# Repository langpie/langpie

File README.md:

# langpie 项目

# 树莓派分布式自动驾驶小车项目-浪派项目
## Respberry Pi LangPie Open Source Project

## 项目目标
* V1.0 阶段: 让树莓派小车能够跑起来(浪)
* V2.0 阶段: 让树莓派能够狠狠的浪(例如加入机器视觉)
* V3.0 阶段: 让树莓派能够狂浪(能够浪到指定地点)
* V4.0 阶段: 让每个人的树莓派能够一起浪(浪派对)
* V5.0 阶段: 让树莓派能够用神经网络自己判断自己该去哪里浪(放浪形骸)
* V6.0 阶段: 树莓派贾维斯浪催的小犊子(没谱)

## 目前状态
### V1.0 版本
- [ ] 电路图绘制
- [ ] 机械图绘制
- [ ] 电路图 Layout
- [ ] 电路板打板
- [ ] 购买元器件
- [ ] 设备焊接
- [ ] 小车组装
- [ ] 树莓派系统安装
- [ ] wiringPi 安装调试
- [ ] 测试电源
- [ ] 测试充电
- [ ] 测试马达
- [ ] 测试树莓派驱动
- [ ] 测试 OLED 屏幕
- [ ] 测试LED 灯
 
## 项目组成员 including Email：

* 圈圈  bg3mdo#langpie.ga
* 漂移菌  yoyojack#langpie.ga
* DoubleDog  doubledog#langpie.ga
* hahaha  hahaha#langpie.ga
* 刘津屹  liujinyi#langpie.ga
* 中华绘图铅笔  pencil#langpie.ga
* 飞鸿  bg3nit#langpie.ga
* 洋洋大叔  bi3qdn#langpie.ga
* 祁建鑫  qjx#langpie.ga
* wjcwqc  wjcwqc#langpie.ga
* 小白 dmuxiaobai#langpie.ga
* lqh  lqh#langpie.ga
* kwanghue kwanghue#langpie.ga
* 张翼 zy#langpie.ga
* iChizer0 

##  项目站点 Project website: 

www.langpie.ga

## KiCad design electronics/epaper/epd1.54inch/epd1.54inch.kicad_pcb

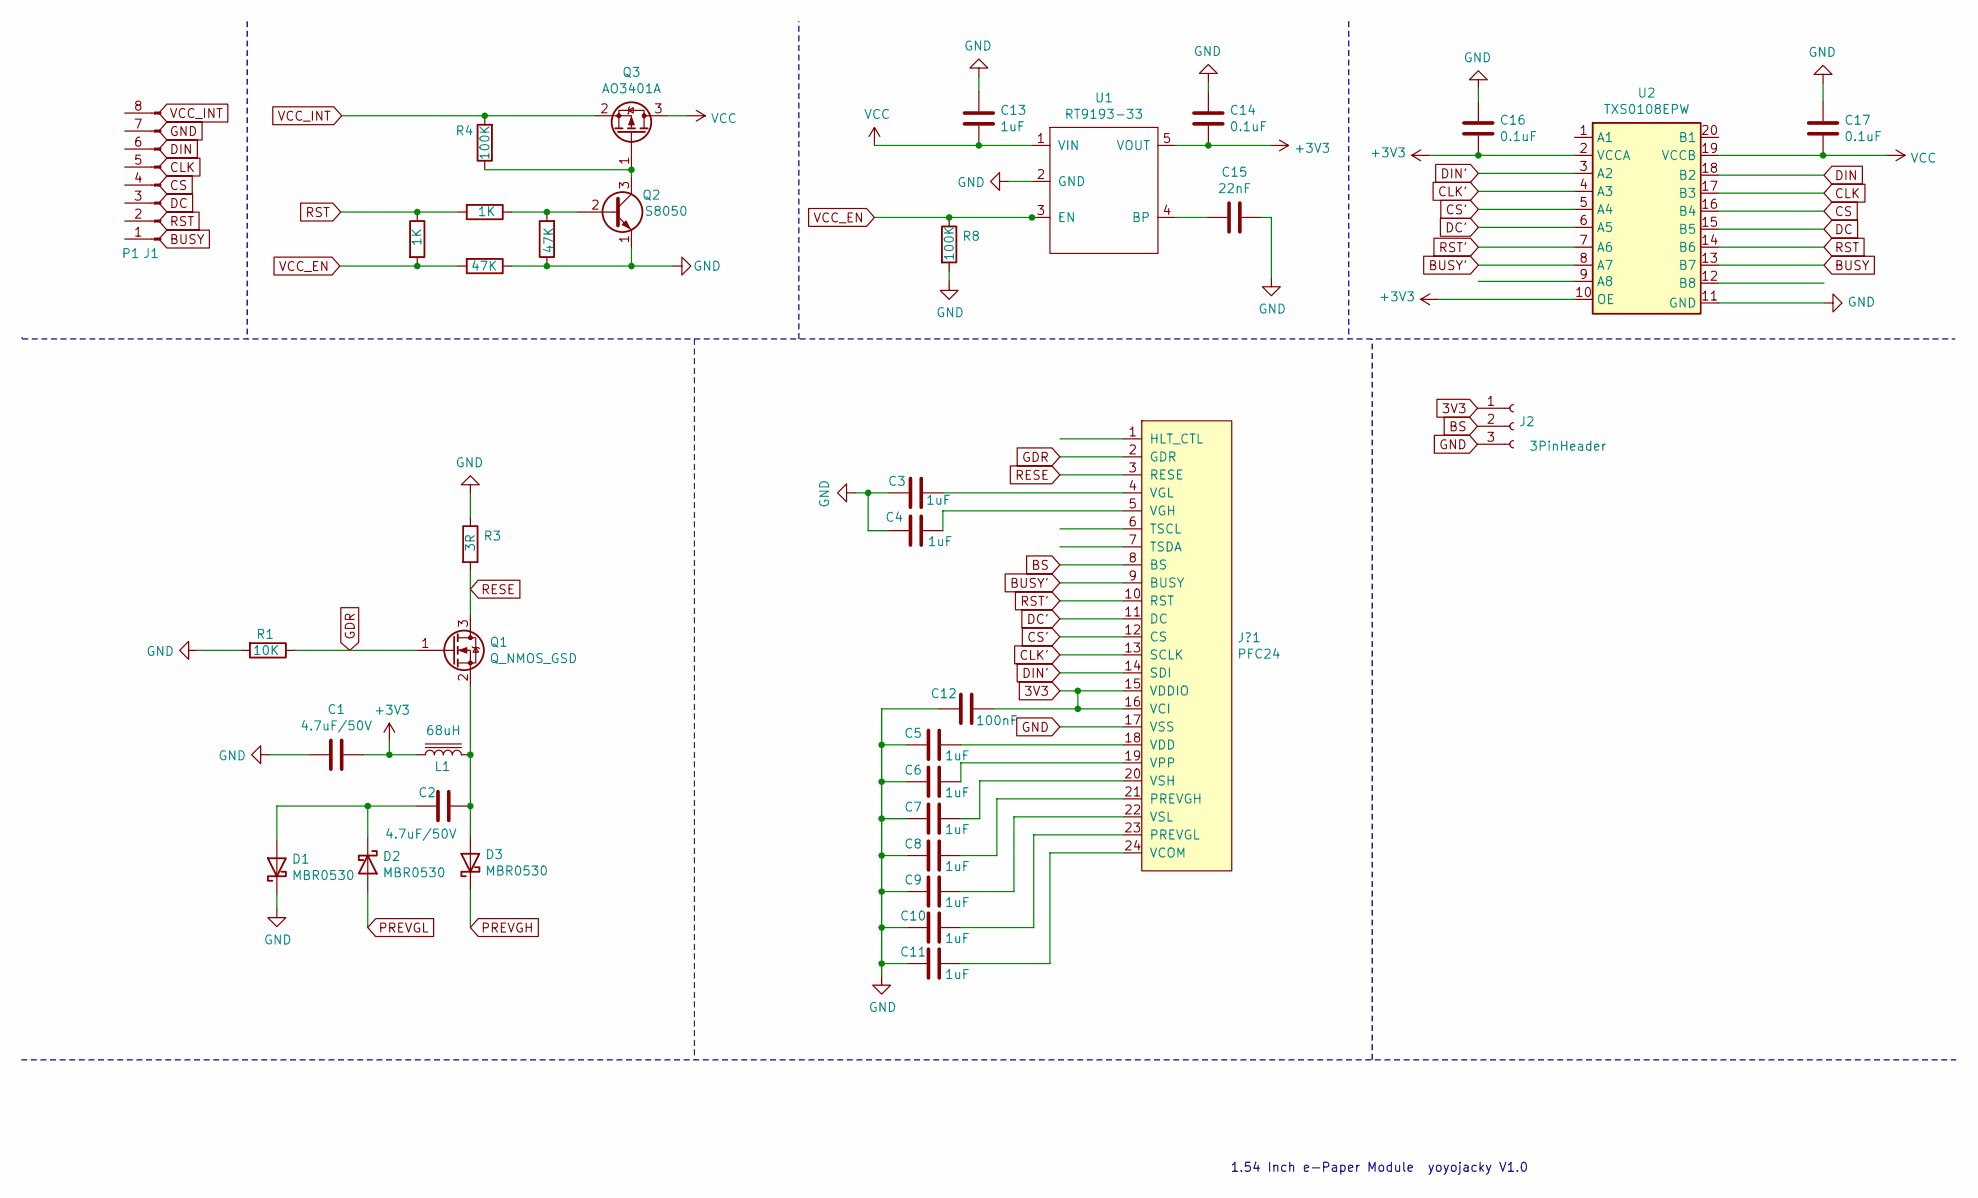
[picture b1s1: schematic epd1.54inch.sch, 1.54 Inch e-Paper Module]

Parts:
C1, C2: 4.7uF/50V; C_0603_1608Metric_Pad1.05x0.95mm_HandSolder
C3, C4, C5, C6, C7, C8, C9, C10, C11, C13: 1uF; C_0603_1608Metric_Pad1.05x0.95mm_HandSolder
C12: 100nF; C_0603_1608Metric_Pad1.05x0.95mm_HandSolder
C14, C16, C17: 0.1uF; C_0603_1608Metric_Pad1.05x0.95mm_HandSolder
C15: 22nF; C_0603_1608Metric_Pad1.05x0.95mm_HandSolder
D1, D2, D3: MBR0530; D_SOD-123
J1: P1; PinHeader_1x08_P2.54mm_Vertical
J2: 3PinHeader; PinHeader_1x03_P2.54mm_Vertical
J?1: PFC24; Hirose_FH12-24S-0.5SH_1x24-1MP_P0.50mm_Horizontal
L1: 68uH; L_10.4x10.4_H4.8
Q1: Q_NMOS_GSD; SOT-323_SC-70_Handsoldering
Q2: S8050; TO-92_Inline
Q3: AO3401A; SOT-23
R1: 10K; R_0603_1608Metric_Pad1.05x0.95mm_HandSolder
R2, R5: 1K; R_0603_1608Metric_Pad1.05x0.95mm_HandSolder
R3: 3R; R_0603_1608Metric_Pad1.05x0.95mm_HandSolder
R4, R8: 100K; R_0603_1608Metric_Pad1.05x0.95mm_HandSolder
R6, R7: 47K; R_0603_1608Metric_Pad1.05x0.95mm_HandSolder
U1: RT9193-33; SOT-23-5
U2: TXS0108EPW; TSSOP-20_4.4x6.5mm_P0.65mm

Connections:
3V3: C12.1, J2.1, J?1.15 (VDDIO), J?1.16 (VCI)
+3V3: C1.1, C14.2, C16.2, L1.1, U1.5 (VOUT), U2.2 (VCCA), U2.10 (OE)
BS: J2.2, J?1.8 (BS)
BUSY: U2.13 (B7)
BUSY': J?1.9 (BUSY), U2.8 (A7)
CLK: U2.17 (B3)
CLK': J?1.13 (SCLK), U2.4 (A3)
CS: U2.16 (B4)
CS': J?1.12 (CS), U2.5 (A4)
DC: U2.15 (B5)
DC': J?1.11 (DC), U2.6 (A5)
DIN: U2.18 (B2)
DIN': J?1.14 (SDI), U2.3 (A2)
GDR: J?1.2 (GDR), Q1.1 (G), R1.1
GND: C1.2, C3.2, C4.2, C5.2, C6.2, C7.2, C8.2, C9.2, C10.2, C11.2, C12.2, C13.2, C14.1, C15.1, C16.1, C17.1, D1.1 (K), J2.3, J?1.17 (VSS), Q2.1 (E), R1.2, R3.1, R6.1, R7.1, R8.2, U1.2 (GND), U2.11 (GND)
unnamed: C2.1, D1.2 (A), D2.1 (K)
unnamed: C2.2, D3.2 (A), L1.2, Q1.2 (S)
unnamed: C3.1, J?1.4 (VGL)
unnamed: C4.1, J?1.5 (VGH)
unnamed: C5.1, J?1.18 (VDD)
unnamed: C6.1, J?1.19 (VPP)
unnamed: C7.1, J?1.20 (VSH)
unnamed: C8.1, J?1.21 (PREVGH)
unnamed: C9.1, J?1.22 (VSL)
unnamed: C10.1, J?1.23 (PREVGL)
unnamed: C11.1, J?1.24 (VCOM)
unnamed: C15.2, U1.4 (BP)
unnamed: Q2.2 (B), R5.1, R7.2
unnamed: Q2.3 (C), Q3.1 (G), R4.1
PREVGH: D3.1 (K)
PREVGL: D2.2 (A)
RESE: J?1.3 (RESE), Q1.3 (D), R3.2
RST: R2.1, R5.2, U2.14 (B6)
RST': J?1.10 (RST), U2.7 (A6)
VCC: C13.1, C17.2, Q3.3 (D), U1.1 (VIN), U2.19 (VCCB)
VCC_EN: R2.2, R6.2, R8.1, U1.3 (EN)
VCC_INT: Q3.2 (S), R4.2

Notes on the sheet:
1.54 Inch e-Paper Module yoyojacky V1.0

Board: 2 copper layers, 37 parts (0 on the bottom side), 30 nets, no tracks yet.

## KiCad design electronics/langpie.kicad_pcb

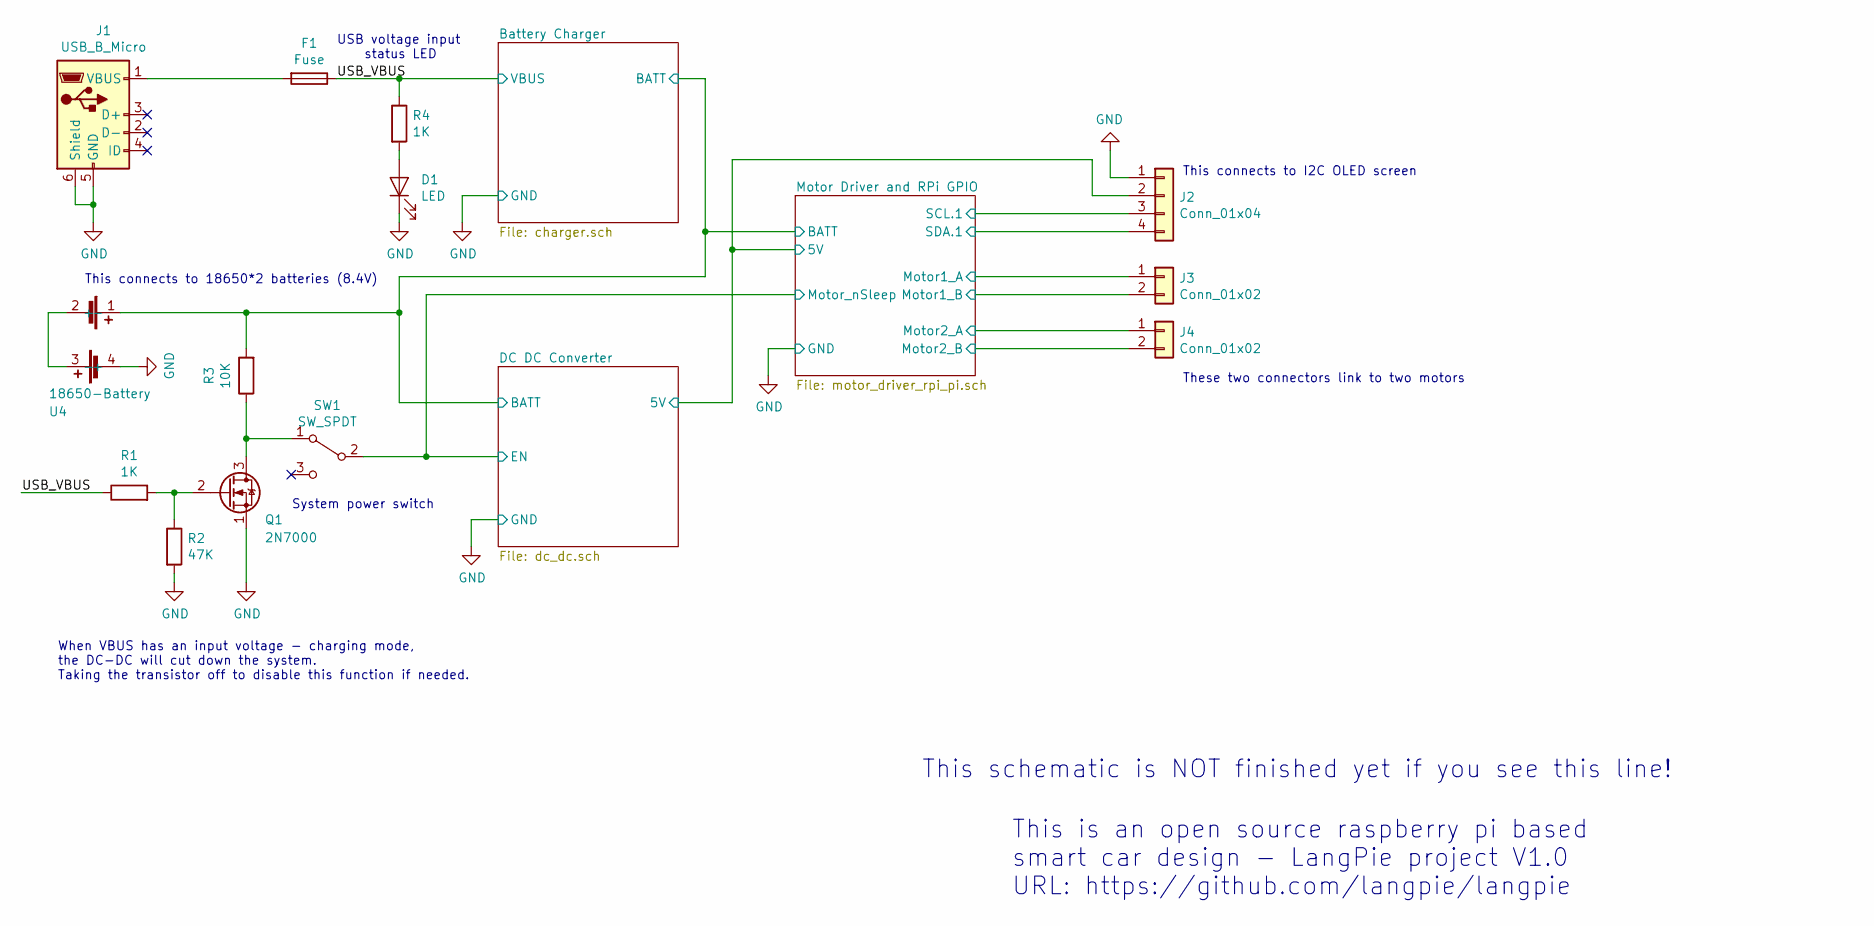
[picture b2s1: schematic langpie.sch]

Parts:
D1: LED; LED_0805_2012Metric
F1: Fuse; Fuse_1206_3216Metric
J1: USB_B_Micro; USB_Micro-B_GCT_USB3076-30-A
J2: Conn_01x04; PinHeader_1x04_P2.54mm_Vertical
J3, J4: Conn_01x02; SolderWirePad_1x02_P5.08mm_Drill1.5mm
Q1: 2N7000; SOT-23
R1, R4: 1K; R_0805_2012Metric
R2: 47K; R_0805_2012Metric
R3: 10K; R_0805_2012Metric
SW1: SW_SPDT; SW_CuK_OS102011MA1QN1_SPDT_Angled
U4: 18650-Battery; li-battery-case

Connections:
/Battery Charger/BATT: R3.2, U4.1 (+); also elsewhere on the board
/DC DC Converter/5V: J2.2; also elsewhere on the board
/DC DC Converter/EN: SW1.2 (B); also elsewhere on the board
/Motor Driver and RPi GPIO/Motor1_A: J3.1; also elsewhere on the board
/Motor Driver and RPi GPIO/Motor1_B: J3.2; also elsewhere on the board
/Motor Driver and RPi GPIO/Motor2_A: J4.1; also elsewhere on the board
/Motor Driver and RPi GPIO/Motor2_B: J4.2; also elsewhere on the board
/Motor Driver and RPi GPIO/SCL.1: J2.3; also elsewhere on the board
/Motor Driver and RPi GPIO/SDA.1: J2.4; also elsewhere on the board
/USB_VBUS: F1.1, R1.1, R4.1; also elsewhere on the board
GND: D1.1 (K), J1.5 (GND), J1.6 (Shield), J2.1, Q1.1 (S), R2.2, U4.4 (-); also elsewhere on the board
unnamed: D1.2 (A), R4.2
unnamed: F1.2, J1.1 (VBUS)
unnamed: Q1.2 (G), R1.2, R2.1
unnamed: Q1.3 (D), R3.1, SW1.1 (A)
unnamed: U4.2 (-), U4.3 (+)

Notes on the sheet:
When VBUS has an input voltage - charging mode, the DC-DC will cut down the system. Taking the transistor off to disable this function if needed.
USB voltage input status LED
This connects to I2C OLED screen
This connects to 18650*2 batteries (8.4V)
These two connectors link to two motors
System power switch
This is an open source raspberry pi based smart car design - LangPie project V1.0 URL: https://github.com/langpie/langpie
This schematic is NOT finished yet if you see this line!

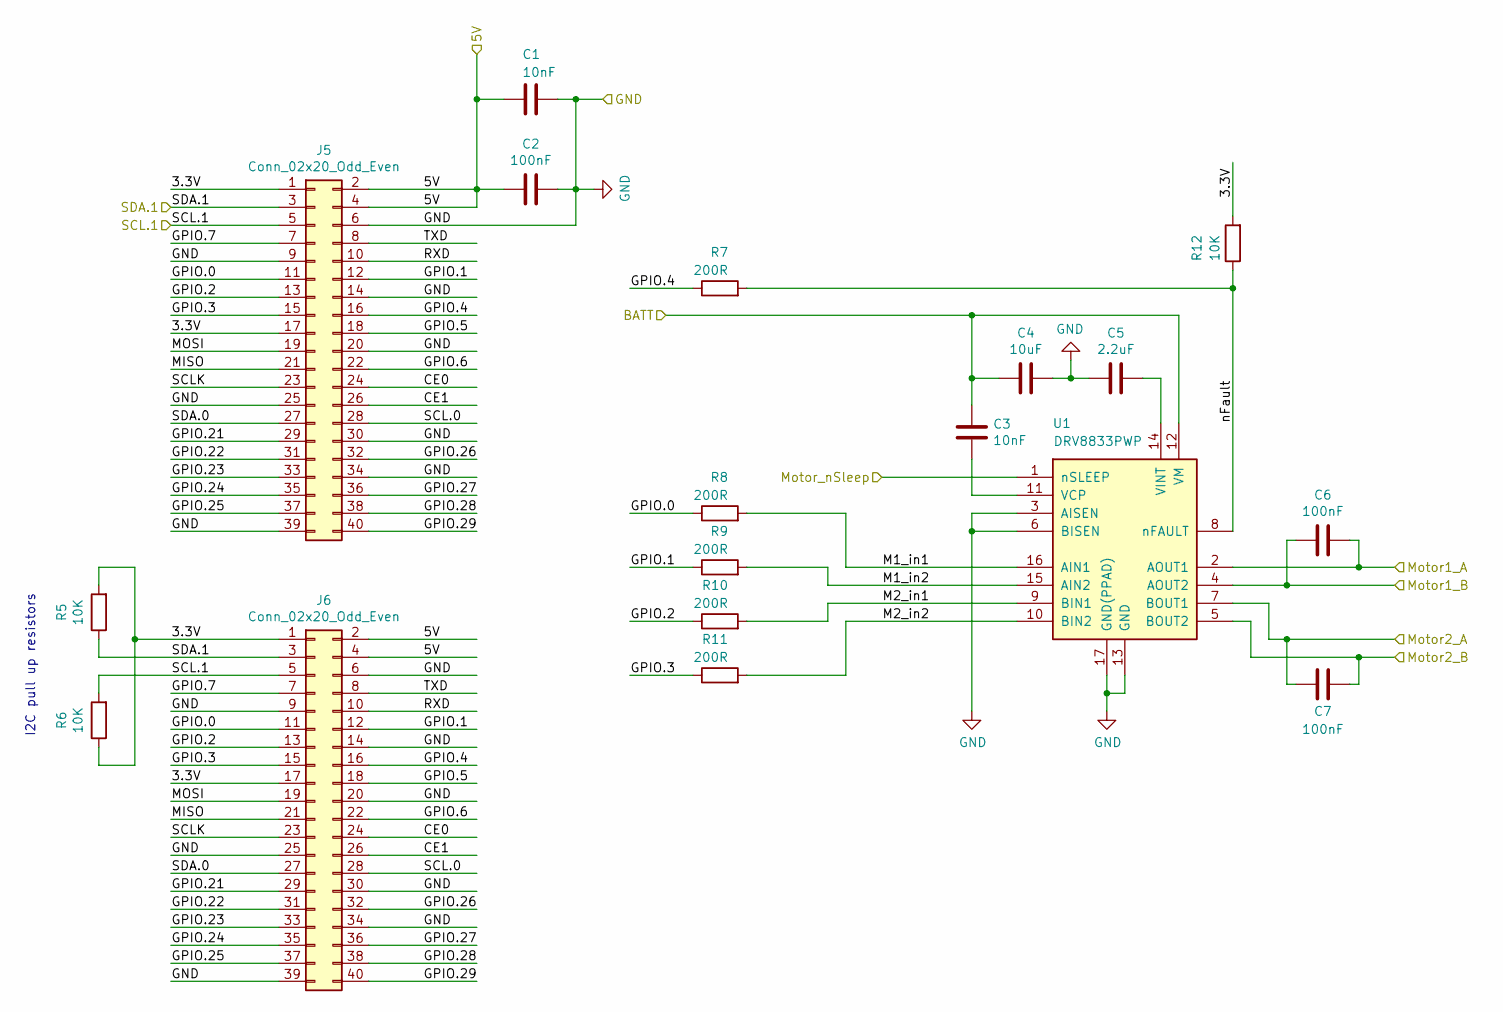
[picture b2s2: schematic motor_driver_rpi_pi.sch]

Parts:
C1, C3: 10nF
C2, C6, C7: 100nF
C4: 10uF
C5: 2.2uF
J5, J6: Conn_02x20_Odd_Even
R5, R6, R12: 10K; R_0805_2012Metric
R7, R8, R9, R10, R11: 200R; R_0805_2012Metric
U1: DRV8833PWP; HTSSOP-16-1EP_4.4x5mm_P0.65mm_EP3.4x5mm_Mask2.46x2.31mm_The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

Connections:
/Battery Charger/BATT: C3.1, C4.2, U1.12 (VM); also elsewhere on the board
/DC DC Converter/5V: C1.2, C2.2, J5.2, J5.4, J6.2, J6.4; also elsewhere on the board
/DC DC Converter/EN: U1.1 (nSLEEP); also elsewhere on the board
/Motor Driver and RPi GPIO/3.3V: J5.1, J5.17, J6.1, J6.17, R5.2, R6.1, R12.2
/Motor Driver and RPi GPIO/CE0: J5.24, J6.24
/Motor Driver and RPi GPIO/CE1: J5.26, J6.26
/Motor Driver and RPi GPIO/GPIO.0: J5.11, J6.11, R8.1
/Motor Driver and RPi GPIO/GPIO.1: J5.12, J6.12, R9.1
/Motor Driver and RPi GPIO/GPIO.2: J5.13, J6.13, R10.1
/Motor Driver and RPi GPIO/GPIO.3: J5.15, J6.15, R11.1
/Motor Driver and RPi GPIO/GPIO.4: J5.16, J6.16, R7.1
/Motor Driver and RPi GPIO/GPIO.5: J5.18, J6.18
/Motor Driver and RPi GPIO/GPIO.6: J5.22, J6.22
/Motor Driver and RPi GPIO/GPIO.7: J5.7, J6.7
/Motor Driver and RPi GPIO/GPIO.21: J5.29, J6.29
/Motor Driver and RPi GPIO/GPIO.22: J5.31, J6.31
/Motor Driver and RPi GPIO/GPIO.23: J5.33, J6.33
/Motor Driver and RPi GPIO/GPIO.24: J5.35, J6.35
/Motor Driver and RPi GPIO/GPIO.25: J5.37, J6.37
/Motor Driver and RPi GPIO/GPIO.26: J5.32, J6.32
/Motor Driver and RPi GPIO/GPIO.27: J5.36, J6.36
/Motor Driver and RPi GPIO/GPIO.28: J5.38, J6.38
/Motor Driver and RPi GPIO/GPIO.29: J5.40, J6.40
/Motor Driver and RPi GPIO/M1_in1: R8.2, U1.16 (AIN1)
/Motor Driver and RPi GPIO/M1_in2: R9.2, U1.15 (AIN2)
/Motor Driver and RPi GPIO/M2_in1: R10.2, U1.9 (BIN1)
/Motor Driver and RPi GPIO/M2_in2: R11.2, U1.10 (BIN2)
/Motor Driver and RPi GPIO/MISO: J5.21, J6.21
/Motor Driver and RPi GPIO/MOSI: J5.19, J6.19
/Motor Driver and RPi GPIO/Motor1_A: C6.1, U1.2 (AOUT1); also elsewhere on the board
/Motor Driver and RPi GPIO/Motor1_B: C6.2, U1.4 (AOUT2); also elsewhere on the board
/Motor Driver and RPi GPIO/Motor2_A: C7.2, U1.7 (BOUT1); also elsewhere on the board
/Motor Driver and RPi GPIO/Motor2_B: C7.1, U1.5 (BOUT2); also elsewhere on the board
/Motor Driver and RPi GPIO/RXD: J5.10, J6.10
/Motor Driver and RPi GPIO/SCL.0: J5.28, J6.28
/Motor Driver and RPi GPIO/SCL.1: J5.5, J6.5, R6.2; also elsewhere on the board
/Motor Driver and RPi GPIO/SCLK: J5.23, J6.23
/Motor Driver and RPi GPIO/SDA.0: J5.27, J6.27
/Motor Driver and RPi GPIO/SDA.1: J5.3, J6.3, R5.1; also elsewhere on the board
/Motor Driver and RPi GPIO/TXD: J5.8, J6.8
/Motor Driver and RPi GPIO/nFault: R7.2, R12.1, U1.8 (nFAULT)
GND: C1.1, C2.1, C4.1, C5.2, J5.6, J5.9, J5.14, J5.20, J5.25, J5.30, J5.34, J5.39, J6.6, J6.9, J6.14, J6.20, J6.25, J6.30, J6.34, J6.39, U1.3 (AISEN), U1.6 (BISEN), U1.13 (GND), U1.17 (GND(PPAD)); also elsewhere on the board
unnamed: C3.2, U1.11 (VCP)
unnamed: C5.1, U1.14 (VINT)

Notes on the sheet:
I2C pull up resistors

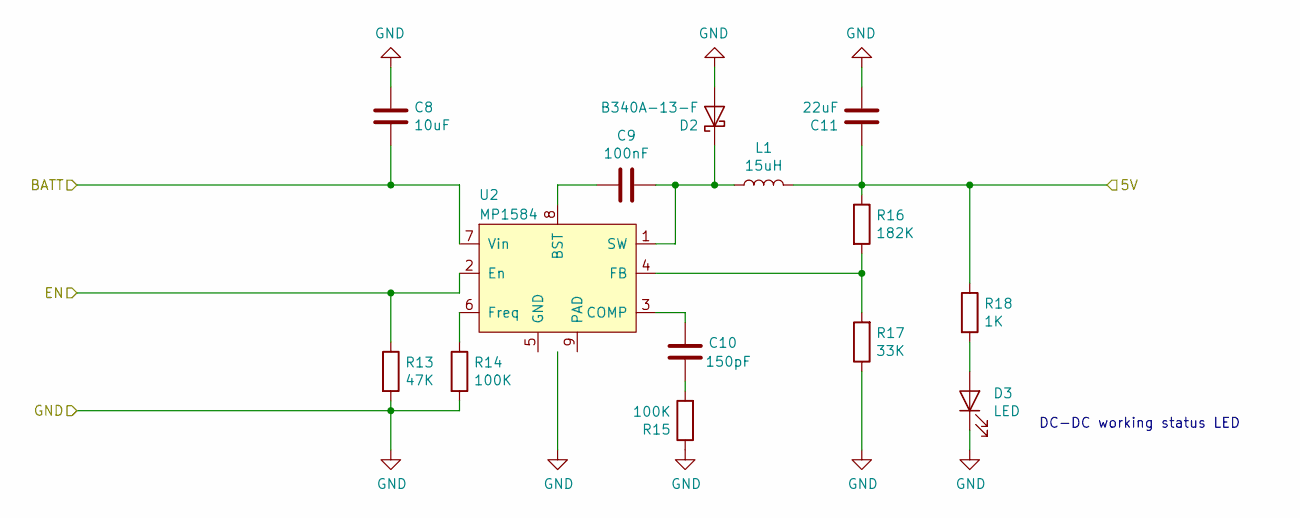
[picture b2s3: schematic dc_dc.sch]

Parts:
C8: 10uF; C_1206_3216Metric
C9: 100nF; C_0805_2012Metric
C10: 150pF; C_0805_2012Metric
C11: 22uF; C_1206_3216Metric
D2: B340A-13-F; D_SMA
D3: LED; LED_0805_2012Metric
L1: 15uH; L_12x12mm_H6mm
R13: 47K; R_0805_2012Metric
R14, R15: 100K; R_0805_2012Metric
R16: 182K; R_0805_2012Metric
R17: 33K; R_0805_2012Metric
R18: 1K; R_0805_2012Metric
U2: MP1584; SOIC-8-1EP_3.9x4.9mm_P1.27mm_EP2.29x3mm_ThermalVias

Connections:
/Battery Charger/BATT: C8.2, U2.7 (Vin); also elsewhere on the board
/DC DC Converter/5V: C11.1, L1.2, R16.1, R18.1; also elsewhere on the board
/DC DC Converter/EN: R13.1, U2.2 (En); also elsewhere on the board
GND: C8.1, C11.2, D2.2 (A), D3.1 (K), R13.2, R14.2, R15.1, R17.1, U2.5 (GND), U2.9 (PAD); also elsewhere on the board
unnamed: C9.1, D2.1 (K), L1.1, U2.1 (SW)
unnamed: C9.2, U2.8 (BST)
unnamed: C10.1, U2.3 (COMP)
unnamed: C10.2, R15.2
unnamed: D3.2 (A), R18.2
unnamed: R14.1, U2.6 (Freq)
unnamed: R16.2, R17.2, U2.4 (FB)

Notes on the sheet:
DC-DC working status LED

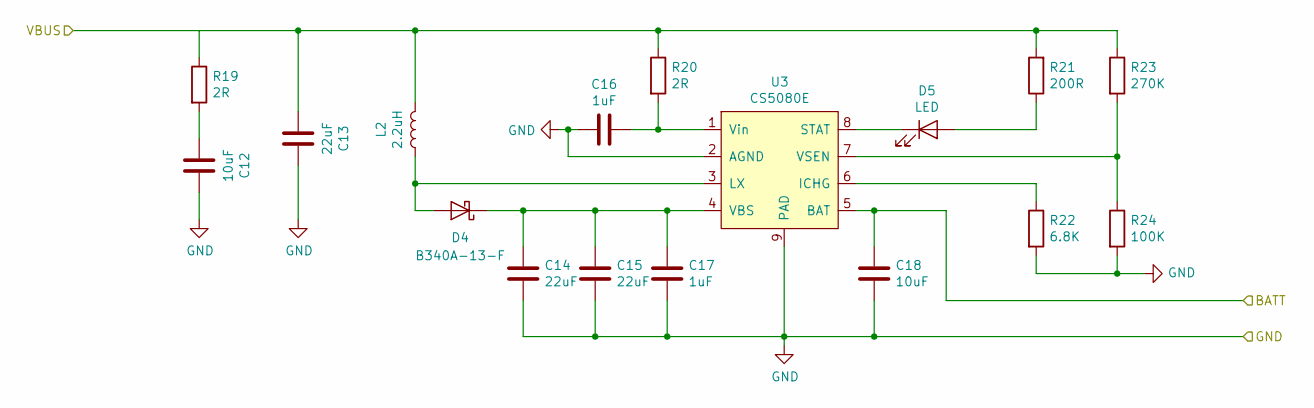
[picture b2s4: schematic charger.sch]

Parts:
C12, C18: 10uF; C_1206_3216Metric
C13, C14, C15: 22uF; C_1206_3216Metric
C16, C17: 1uF; C_0805_2012Metric
D4: B340A-13-F; D_SMA
D5: LED; LED_0805_2012Metric
L2: 2.2uH; L_12x12mm_H6mm
R19, R20: 2R; R_0805_2012Metric
R21: 200R; R_0805_2012Metric
R22: 6.8K; R_0805_2012Metric
R23: 270K; R_0805_2012Metric
R24: 100K; R_0805_2012Metric
U3: CS5080E; SOIC-8-1EP_3.9x4.9mm_P1.27mm_EP2.29x3mm_ThermalVias

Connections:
/Battery Charger/BATT: C18.1, U3.5 (BAT); also elsewhere on the board
/USB_VBUS: C13.2, L2.2, R19.1, R20.1, R21.2, R23.1; also elsewhere on the board
GND: C12.1, C13.1, C14.1, C15.1, C16.2, C17.1, C18.2, R22.2, R24.2, U3.2 (AGND), U3.9 (PAD); also elsewhere on the board
unnamed: C12.2, R19.2
unnamed: C14.2, C15.2, C17.2, D4.1 (K), U3.4 (VBS)
unnamed: C16.1, R20.2, U3.1 (Vin)
unnamed: D4.2 (A), L2.1, U3.3 (LX)
unnamed: D5.1 (K), U3.8 (STAT)
unnamed: D5.2 (A), R21.1
unnamed: R22.1, U3.6 (ICHG)
unnamed: R23.2, R24.1, U3.7 (VSEN)

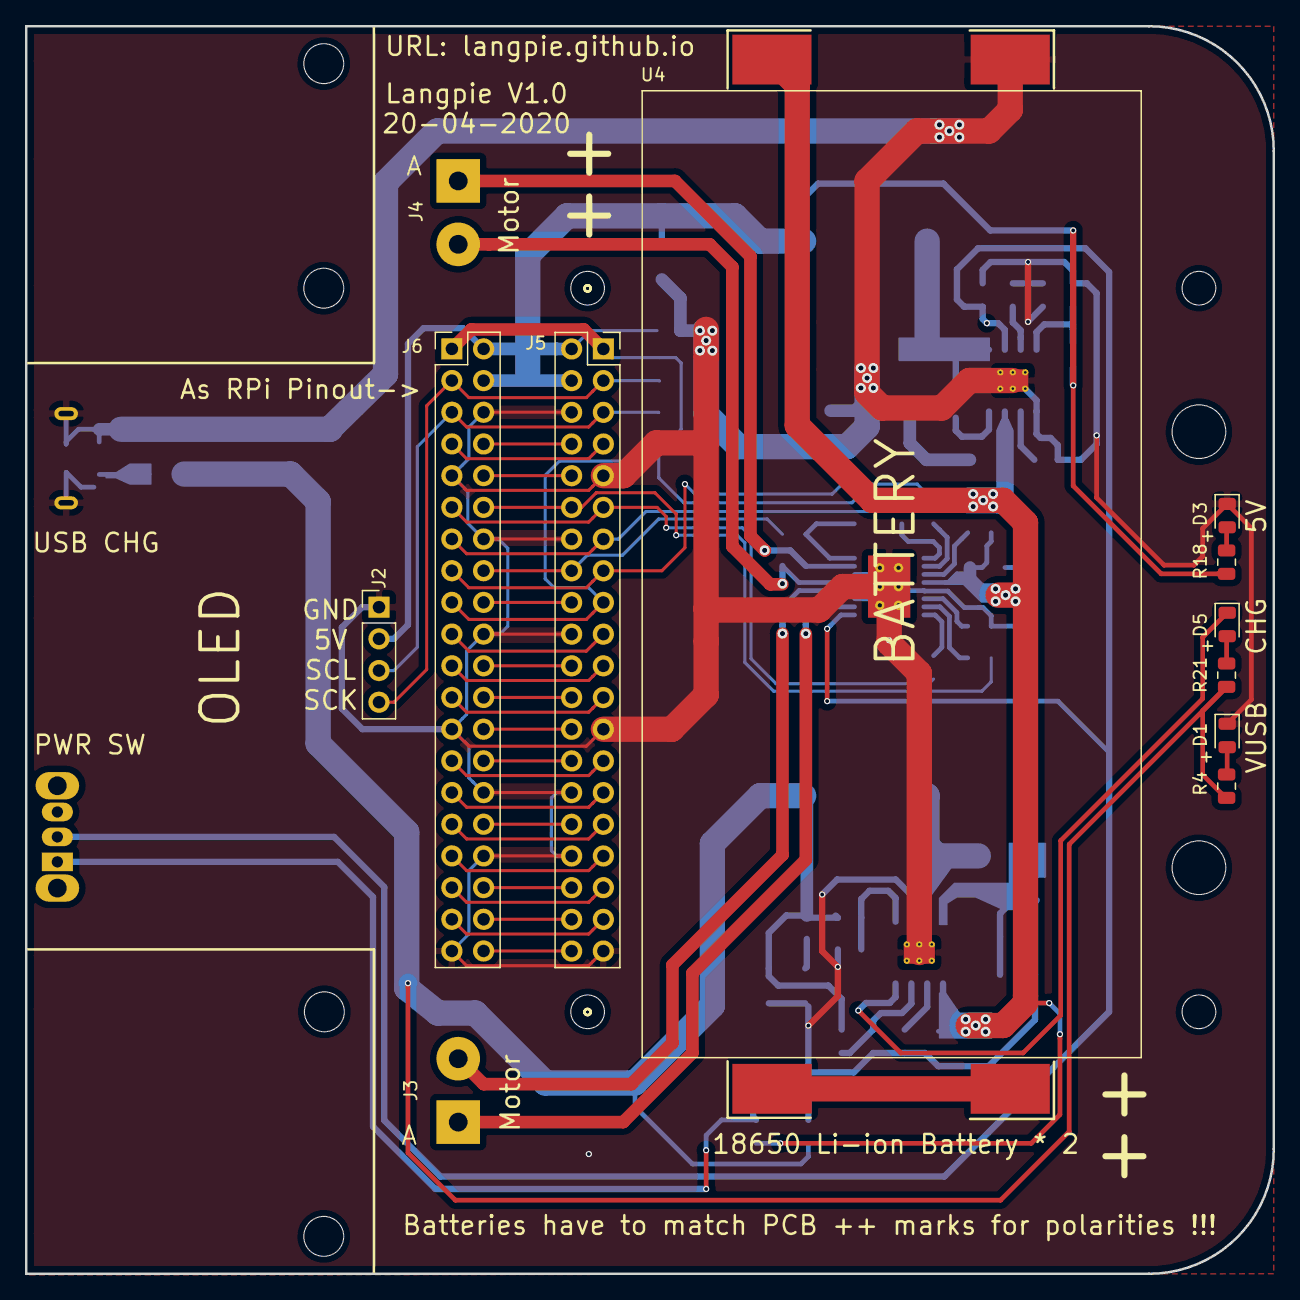
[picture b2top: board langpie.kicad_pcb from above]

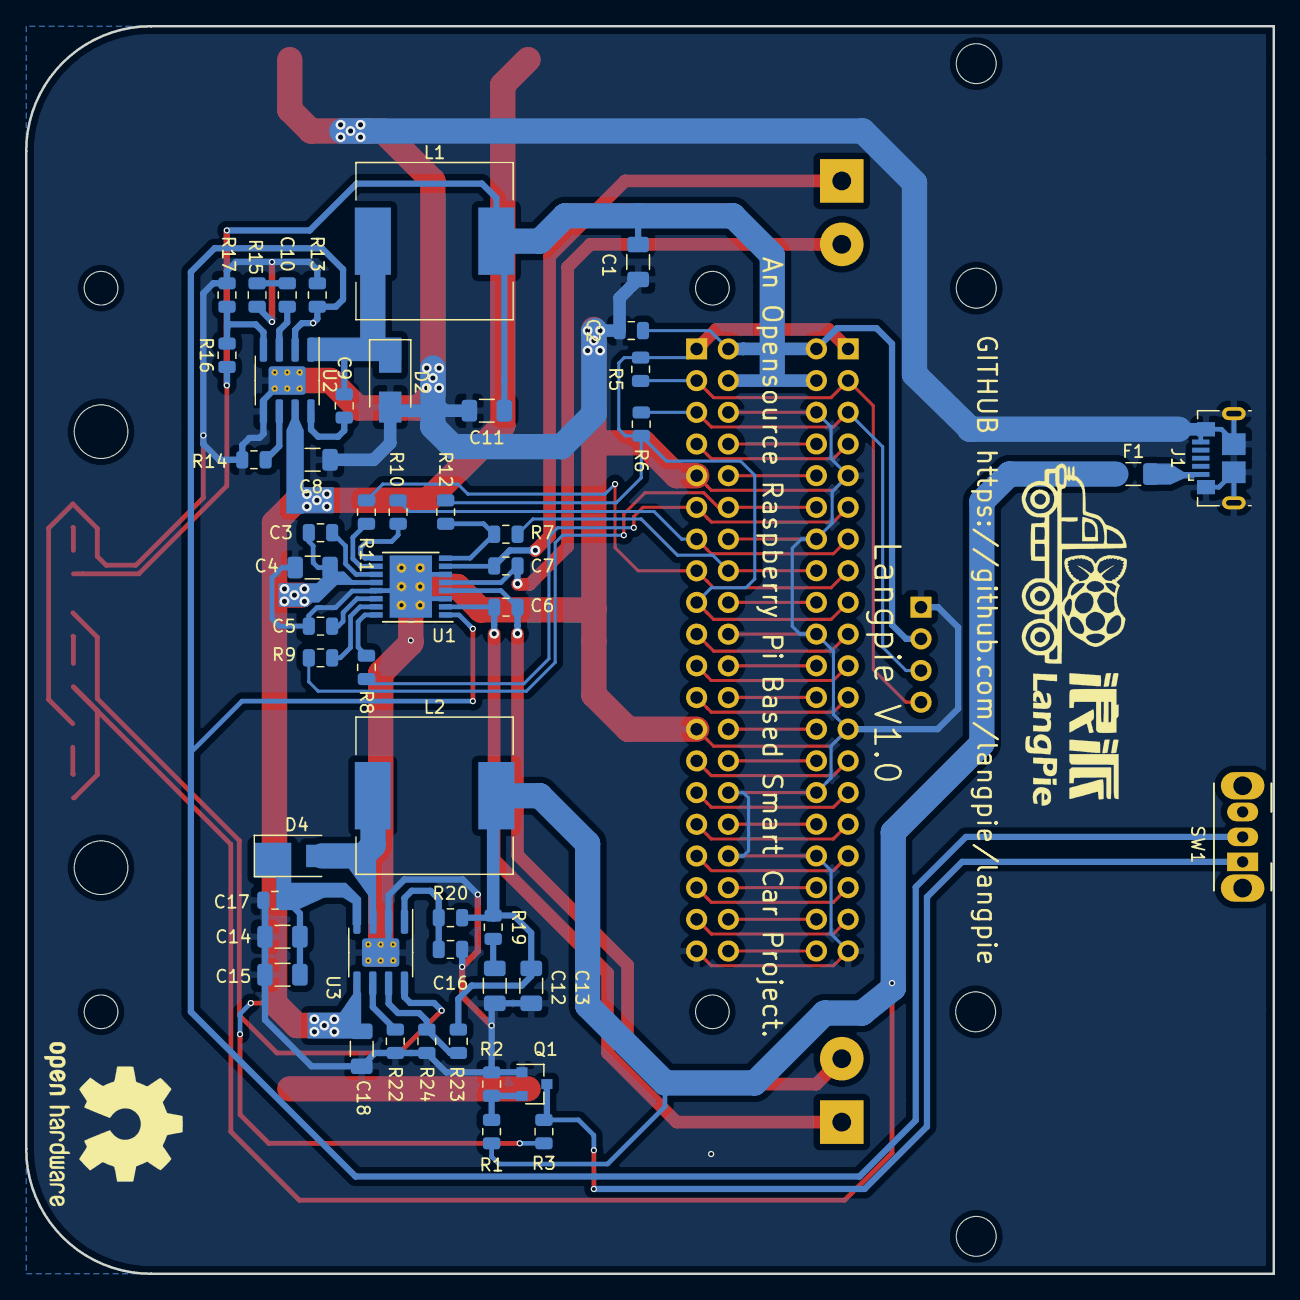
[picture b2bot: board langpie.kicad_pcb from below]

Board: 2 copper layers, 100.0 x 100.0 mm, 72 parts (50 on the bottom side), 65 nets.

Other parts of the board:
 : MountingHole_2.7mm_M2.5
 #2,  #3: MountingHole_4.3mm_M4
 #4,  #5,  #6: MountingHole_2.7mm_M2.5
 #7,  #8,  #9,  #10: MountingHole_3.2mm_M3

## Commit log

2020-04-06 update site file
2020-04-06 update docs
2020-04-06 Set theme jekyll-theme-hacker
2020-04-06 cleanup
2020-04-07 Change one folder to 'mechanics', update electronics and pi 3d step file.
2020-04-07 md update
2020-04-08 upload software list.
2020-04-09 提交信息
2020-04-10 优化了电机座增加了摄像头支架并创建了3D打印所需的STL文件
2020-04-10 Change electronics design, update new SCHs...
2020-04-10 Adding some V1.0 project images
2020-04-10 update RPi GPIO SCH
2020-04-10 update Raspberry pi preparation file and update email list
2020-04-10 update auto add tsinghua source list
2020-04-11 Slightly change electronics
2020-04-12 Update DCDC design, add a DCDC output calculator tool, add oled screen 3D models
2020-04-12 Change to electronics, and adding pi dimensions into documents
2020-04-12 Preview SCH is done, but not fully finished.
2020-04-12 A bug fix in electronics
2020-04-13 更新了V1.1版本的小车待完善
2020-04-13 基本完善了V1.1版本的小车
2020-04-14 改进了V1.1版本的小车
2020-04-14 Electronics define IOs to motor driver.
2020-04-14 modified: ../../electronics/charger.sch modified: ../../electronics/charger.sch-bak modified: ../../electronics/dc_dc.sch modified: ../../electronics/dc_dc.sch-bak modified: ../../electronics/langpie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
2020-04-15 update pcb file and netlist
2020-04-18 Adding PCB and PCB library
2020-04-18 Finish PCB, silightly change to SCH, Gerber generated, V1.0 HW almost done.
2020-04-19 Finalise the design and send to manufactory already for the V1
2020-04-25 Adding real PCB look pictures.
2020-09-10 add 1.54inch e-paper for langpie with schematic
